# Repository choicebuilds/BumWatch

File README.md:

# BumWatch

THIS WATCH CONSISTS ENTIRELY OF BREAKOUT BOARDS AND IN-HOUSE FABRICATED PCBs. I was unable to make this version work on a PCB due to voltage regulator issues. So, I switched to the protoboard. If you plan on replicating this project, please do yourself a favor and add a functional buck converter. I created a significantly improved version here: https://github.com/choicebuilds/JWatch

## Introduction

The Bumwatch is truly made for bums - it has all the features a bum needs and nothing else. A very minimalistic display displays two things - steps taken and their heart rate that updates every second. 

We live in a world full of distractions and bum-inducing items. Technology is specifically designed to make our lives easier, which is synonymous with making us more of a bum. Instead of bleeding-edge features, what a bum needs is an accountability partner that gives them only what they truly need.

The BumWatch provides the satisfaction of progress through step counting that updates live to provide instant gratification and feedback. Also, knowing the average resting heart rate is 60-100, this would motivate the bums to lower their heartrate through exercise because they become aware they are a bum. Finally, when the bum idles for too long, there is a vibration feedback that reminds them they are a bum. If you want to stop being a bum, there is no better method than to create this watch.

This iteration of the BumWatch is made entirely in-house and costed $0 (not including time and labor). The BumWatch consists entirely of breakout boards (that I borrowed) placed and stacked neatly and soldered to a custom-PCB that was created using in-house PCB fabrication machines (I could not complete this part, so I used protoboards). Although I would never recommend this method (due to problems I will address as we go on), it was fun planning and watching everything come to fruition.

## PCB Fabrication
Essentially, you can use any electrical CAD software (I used KiCAD) to create a schematic and layout. Then, you export the Front Side Copper (gbr), Back Side Copper (gbr), Edge Cuts (gbr), and Drill Files (drl). Why only these four? Well, the available PCB fabrication machines in-house (LPKF Protomat and Protolaser) from my local makerspace makes it extremely limited for a few reasons:

1. You cannot create vias - this makes layout extremely difficult since you have to cram everything on one side. In other words, every trace has to be on the back side since through-hole soldering without vias makes it so that the front side is not electrically connected. This also makes the watch larger than necessary.
2. You cannot create solder mask or silkscreen - not exactly an issue for fabrication, but a giant headache for soldering & assembly (more on the PCB assembly section).

Is it still doable? Absolutely.
Does it look cooler? Absolutely (lie).
Will I ever do it again? Absolutely NOT.
The time and effort spent on laying it out and assembling it highly outweighs just ordering a PCB from say JLCPCB. I was unable to do this since I was not able to order them on time (due to US customs taking forever) and falling victim to sunk cost.

We'll get to why I had to make two iterations (yet still failed to make the final version) down the line.

## Materials

1x Arduino Pro Mini (MUST BE 3.3V Version)
- Small lipo batteries usually say they supply 3.7V. However, it will drop down from 4.2V when fully charged to 3.0V when fully discharged until it eventually gives out. So, either the breakouts must be rated within the 3.0V-4.2V range or we must use a voltage regulator/buck converter. Nevertheless, it has to be a 3.3V rated version unless you use a step-up converter that can supply 5V. Update: the voltage regulator on this one also had a 1V-1.1V dropout, so I ended up using an Arduino Nano.

1x SSD1306 (4-pin display)
- This was the only display I could find that fit my desired form factor that I could find in-person. There were many more options online, but I settled on this one since this version of the watch is not exactly the final version I want to use (i.e. I did not care).

1x Sparkfun ICM-20948 Breakout (IMU)
- The disadvantage of this one over the BNO055 (this was so old and inaccurate it was unusable) is that there is no integrated sensor fusion, meaning it displays the raw IMU data. However, this sensor is much newer and much more accurate than all the alternatives I have considered. In essence, it is better in every way as long as I can write an accurate step counter algorithm.

1x Sparkfun MAX30101 + MAX32664 Breakout (Pulse Oximeter and HR Monitor)
- The cool thing about this breakout is that it has a MAX32664 attached to it. The sole purpose of that chip is to take the raw data from the MAX30101 and use its internal algorithm to display the heart rate without me having to write any algorithms - very convenient.

1x Sparkfun BPM085 Breakout (Pressure Sensor)
- This ended up not being used in the final design because it was the only sensor rated at 1.8V-3.6V and the voltage regulator was a piece of junk. Also, I forgot to route the voltage regulator to the on/off switch meaning this sensor would always be on with the voltage regulator - as mentioned in the PCB Fabrication section, I ran out of time so I could not fix this issue.

1x Adafruit DRV2605L Breakout
- Every sensor above gave me a headache at some point for one reason or another, but this one just worked. Maybe Adafruit is superior to Sparkfun? (this is a joke.. or is it)

1x Vibration Motor
- Okay I lied, this isn't a breakout. But like you need a vibration motor to use the vibration motor driver right? This one is brand agnostic - just find a small vibration motor that fits your watch.

1x Adafruit USB-C Microlipo Breakout (USB-C Charging)
- Essentially, you can use this to charge/discharge your battery. It's only supports charging though, you do not use this to update your Arduino firmware. And also, it just works (to be fair, all the Sparkfun sensors had more complex wiring diagrams)

1x 3.3V Voltage Regulator
- I got this from my local makerspace and it was really, REALLY bad. The voltage drop after connecting one sensor was so large my multimeter displayed <3V (???). Luckily, all the sensors here except the BMP085 were rated 3V-5.5V, so I did not need this voltage regulator (i.e. I could connect it directly to the battery since it will always stay within 3V-4.2V.. update: the pro mini also had a terrible voltage regulator that outputted something along 2.7V). Due to this garbage of a regulator, I had to redo my entire layout and print an entire new circuit boards just because this voltage regulator was so bad (rant over). Why not use a buck converter? Simplicity and form factor of course. Also, this only crossed my mind after I created a layout that fit the smartwatch form factor. And considering this was not even the final version, I just could not bother to waste any more time on this. Please use a buck converter.

1x 3.7V LiPo Battery
- Pretty self-explanatory here, just find one that's not a coincell battery and is small enough to fit inside your watch.

1x On/Off Switch
- This can be any switch. It essentially creates an open circuit between the battery and all the sensors in order to save power when not used.

1x FTDL Basic Breakout (USB to Serial Converter)
- THIS IS NOT APART OF THE WATCH. The Arduino pro mini does not have a convenient port to update the firmware. So, you actually need this breakout to be able to push your Arduino sketches into the Arduino pro mini.

## Assembly

This part was a massive headache. I've soldered on a PCB with no solder mask or silkscreen before, but this one just caused a lot more problems than I would have liked. This was exponentially harder than the one I made before due to a lot of issues:

1. Not everything is connected in the layout - the first layout was perfect and everything would have worked out if the voltage regulator did not have problems. However, the second layout was made throughout an all-nighter the day before my local makerspace was going to close. I thought of a brilliant plan to bypass vias because things were not connecting properly on time. Instead of connecting everything on the back side, I decided to connect all my 3.7V on the front side and create a singular via with a very short wire and solder to connect the front and back side. This only works if there are vias for every 3.7V holes. Since the makerspace was closed, I could not make another PCB with a proper layout.

2. Misplaced sensors and improper traces - I flipped the pressure sensor backwards (it was right the first time, I don't even know how this happened) and the 3.7V on the voltage regulator comes straight from the battery instead of the on/off switch. I decided to add an on/off switch last minute, and I probably should not have made major changes before the deadline.

3.  The pins are pre-soldered onto the breakout - this should not have been a problem if problems 1 and 2 did not exist. However, in order to connect the 3.7V on the front side and remove a few pins to make layout easier (and more compact), I had to unsolder the pins and resolder them back together to connect them properly. Lesson learned - always, always double check your design before fabrication and do not trust your brain during an all-nighter.

4. The through-hole copper is fragile - since I was not sure I had access to flux after the makerspace closed, I sanded the final PCB very hard with sandpaper over running water to prevent oxidation. Bad idea. After soldering, the copper surrounding the all the through-holes would fall off with the sensors if I yanked too hard. Either that or it probably happened due to having to unsolder/resolder many things due to the issues mentioned above. So, I had to manually create traces whenever this happened.

5. Continuity Issues - I learned from the previous PCB I fabricated to make huge clearances. However, I finished half of it and came back after a week to realize there were my GND was connected to my SCL pin for some reason (?). After using an exacto knife to scratch around every single contact point, it was not a problem; but, the lack of solder mask and silkscreen is truly a pain.

You can stack the breakout boards together to reduce space. Also, you can cut the wires after soldering them to make them take up less space.

## Software

This part is extremely simple - it was a matter of copying preexisting libraries from the breakout boards and piecing them together. Here are the libraries for reference:

Display: https://github.com/adafruit/Adafruit_SSD1306
IMU: https://github.com/sparkfun/SparkFun_ICM-20948_ArduinoLibrary
HR Sensor: https://github.com/sparkfun/SparkFun_Bio_Sensor_Hub_Library
Pressure Sensor: https://github.com/adafruit/Adafruit-BMP085-Library
Vibration Motor: https://github.com/adafruit/Adafruit_DRV2605_Library

The only difficult part was processing the IMU data and creating a step counting algorithm. With the help of AI, I essentially combined the movement of all axes and if that was greater than a certain threshold, it was counted as a step. Then, I set a cooldown period based on the average human step pace in order to avoid double counting. This only works if the user is actively swinging their arms while walking - putting your hands in your pocket would lead to inaccurate results. Considering this is a first prototype, I was satisfied with this.

## Mechanical CAD (3D Printing)

If I did not have to redesign everything due to my voltage regulator, this would have looked much better. However, due to the frustration of everything stated above, I just created a bare minimum chassis for a working demo. Even then, it turns out I printed the wrong size before the 3D printing station had to shut down due to it being the end of the semester. Oh well.

## Protoboarding

With all the power issues, I still wanted to make a final product. So, I decided to create a 4-layer protoboard watch in order to fit a watch form factor. After hours of soldering, I got tired of continuity testing. This ultimately meant I could not use half the sensors because there were continuity issues for my lower 2 layers. However, I was still able to create a working IMU and step counter. This product is no longer in development & I will be focusing all my efforts on the JWatch (link above). Here are some pictures for reference:

## Conclusion

There are a lot of issues with this product. But all in all, with the fixes I mentioned above, I was able to create a functional product that works as intended, albeit not on the PCB. If anyone wants to expand upon this, please use a buck converter (step up if you wanna use 5V Arduinos, step down if you intend to use the pressure sensor or want consistent 3.3V output). Also, I would lay it out more compactly and properly with a professional PCB. Finally, the mechanical CAD is very bare-bones - there's much to improve in this aspect. I am satisfied with what I made since it was only a stepping stone to something bigger. I believe replicating this project as-is and making a working final product would be very helpful if you want to sharpen your debugging skills (please don't, you'll lose your hair over this).

## Working Demo

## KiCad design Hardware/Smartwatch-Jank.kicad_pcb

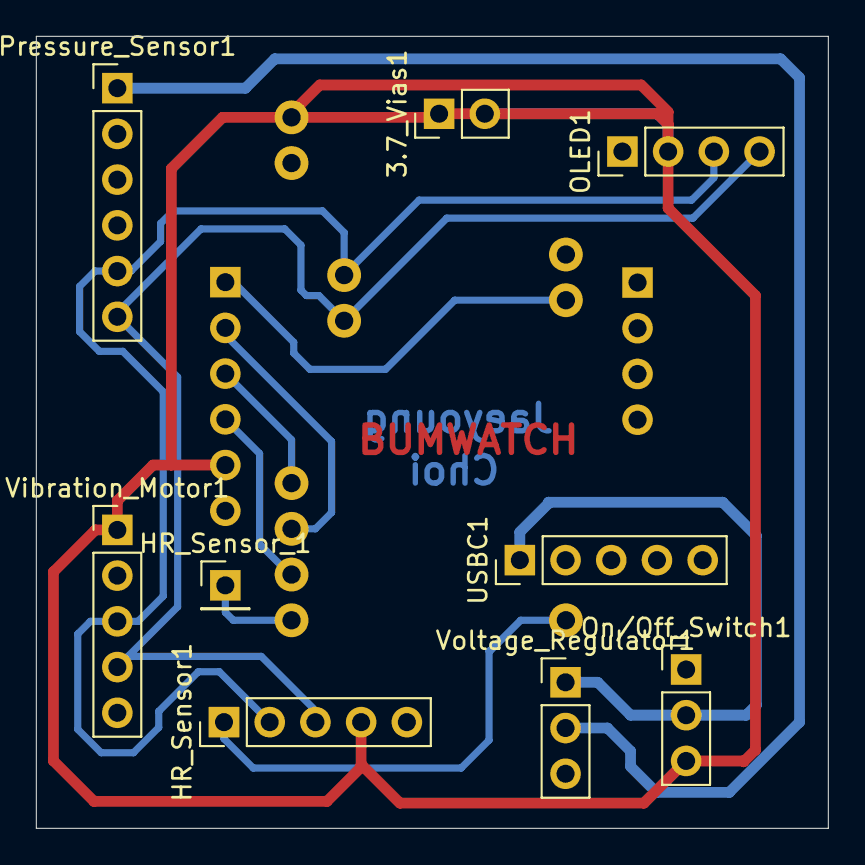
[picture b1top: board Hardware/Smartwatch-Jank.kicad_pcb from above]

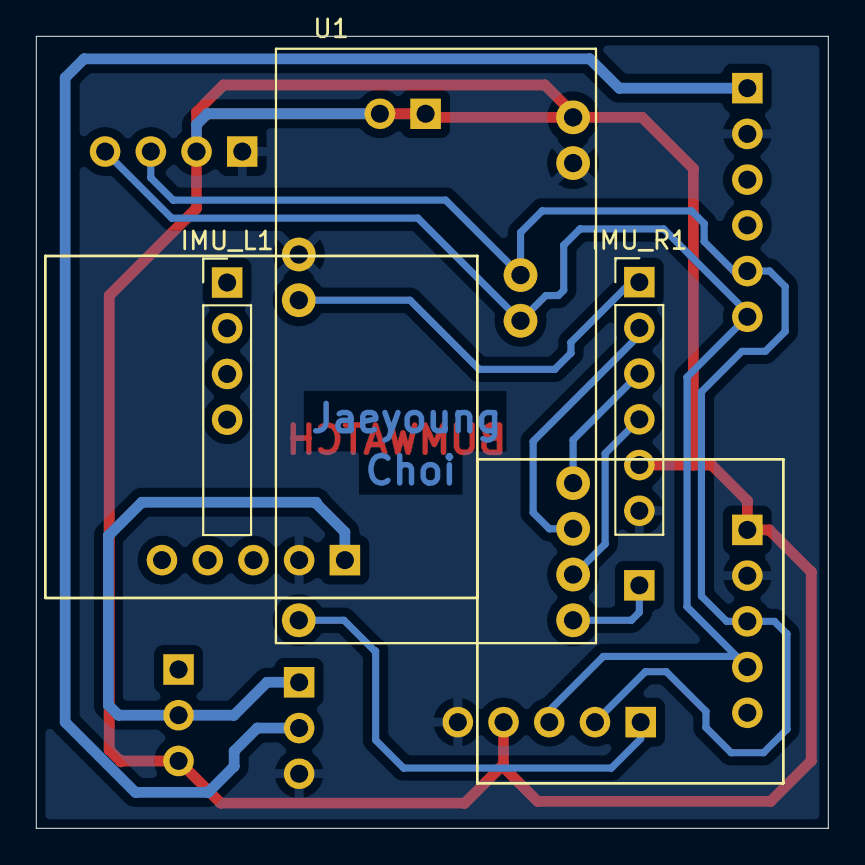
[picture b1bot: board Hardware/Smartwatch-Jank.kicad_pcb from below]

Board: 4 copper layers, 44.0 x 44.0 mm, 12 parts (3 on the bottom side), 12 nets.

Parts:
3.7_Vias1: Conn_01x02; PinHeader_1x02_P2.54mm_Vertical
HR_Sensor1: Conn_01x05; PinHeader_1x05_P2.54mm_Vertical
HR_Sensor_1: Conn_01x01; PinHeader_1x01_P2.54mm_Vertical
IMU_L1: Conn_01x06; PinHeader_1x06_P2.54mm_Vertical
IMU_R1: Conn_01x06; PinHeader_1x06_P2.54mm_Vertical
OLED1: Conn_01x04; PinHeader_1x04_P2.54mm_Vertical
On/Off_Switch1: Conn_01x03; PinHeader_1x03_P2.54mm_Vertical
Pressure_Sensor1: Conn_01x06; PinHeader_1x06_P2.54mm_Vertical
U1: ARDUINO_PRO_MINI; MODULE_ARDUINO_PRO_MINI
USBC1: Conn_01x05; PinHeader_1x05_P2.54mm_Vertical
Vibration_Motor1: Conn_01x05; PinHeader_1x05_P2.54mm_Vertical
Voltage_Regulator1: Conn_01x03; PinHeader_1x03_P2.54mm_Vertical

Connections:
/3.3: Pressure_Sensor1.1, Voltage_Regulator1.2
/3.7: 3.7_Vias1.1, 3.7_Vias1.2, HR_Sensor1.4, IMU_R1.5, OLED1.2, On/Off_Switch1.3, U1.JP6_1 (RAW), Vibration_Motor1.1
/BAT: On/Off_Switch1.2, USBC1.1, Voltage_Regulator1.1
/CS: IMU_R1.1, U1.JP7_8 (D2)
/D9: HR_Sensor1.1, U1.JP7_1 (D9)
/D10: HR_Sensor_1.1, U1.JP6_12 (D10)
/MISO: IMU_R1.2, U1.JP6_10 (MISO)
/MOSI: IMU_R1.4, U1.JP6_11 (MOSI)
/SCK: IMU_R1.3, U1.JP6_9 (SCK)
/SCL: HR_Sensor1.2, OLED1.3, Pressure_Sensor1.5, U1.JP2_2 (A5), Vibration_Motor1.3
/SDA: HR_Sensor1.3, OLED1.4, Pressure_Sensor1.6, U1.JP2_1 (A4), Vibration_Motor1.4
GND: HR_Sensor1.5, IMU_R1.6, OLED1.1, Pressure_Sensor1.2, U1.JP6_2 (GND_1), U1.JP7_9 (GND_2), USBC1.2, Vibration_Motor1.2, Voltage_Regulator1.3

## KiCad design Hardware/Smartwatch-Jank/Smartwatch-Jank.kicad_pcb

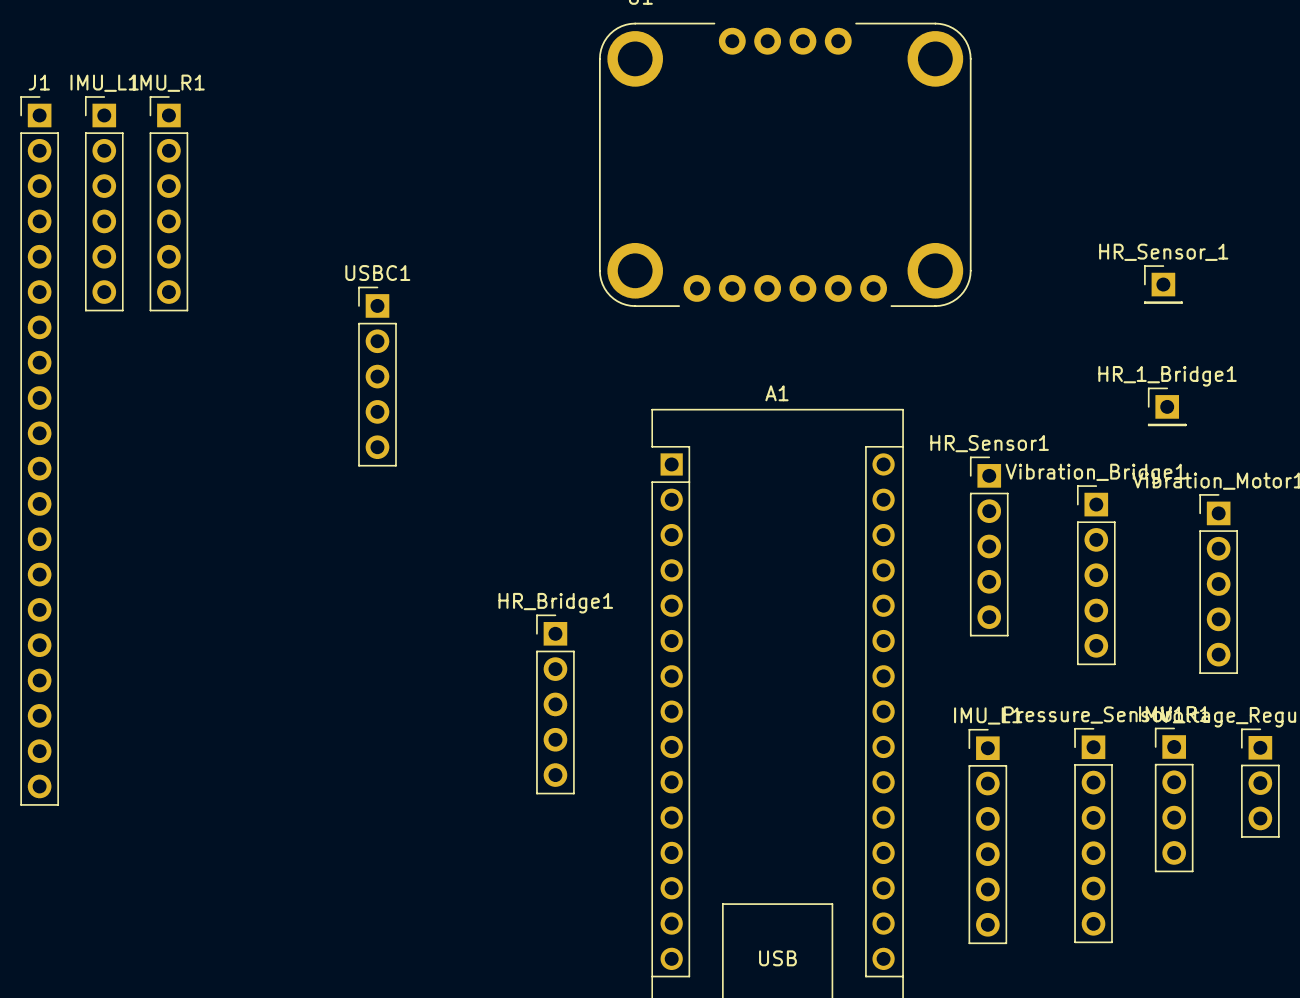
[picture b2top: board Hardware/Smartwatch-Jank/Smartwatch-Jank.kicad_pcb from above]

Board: 4 copper layers, 16 parts (0 on the bottom side), 21 nets, no tracks yet.

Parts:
A1: Arduino_Nano_Every; Arduino_Nano
HR_1_Bridge1: Conn_01x01; PinHeader_1x01_P2.54mm_Vertical
HR_Bridge1: Conn_01x05; PinHeader_1x05_P2.54mm_Vertical
HR_Sensor1: Conn_01x05; PinHeader_1x05_P2.54mm_Vertical
HR_Sensor_1: Conn_01x01; PinHeader_1x01_P2.54mm_Vertical
IMU_L1, IMU_L1#2: Conn_01x06; PinHeader_1x06_P2.54mm_Vertical
IMU_R1: Conn_01x06; PinHeader_1x06_P2.54mm_Vertical
IMU_R1#2: Conn_01x04; PinHeader_1x04_P2.54mm_Vertical
J1: Conn_01x20; PinHeader_1x20_P2.54mm_Vertical
Pressure_Sensor1: Conn_01x06; PinHeader_1x06_P2.54mm_Vertical
U1: 2472; BNO055
USBC1: Conn_01x05; PinHeader_1x05_P2.54mm_Vertical
Vibration_Bridge1: Conn_01x05; PinHeader_1x05_P2.54mm_Vertical
Vibration_Motor1: Conn_01x05; PinHeader_1x05_P2.54mm_Vertical
Voltage_Regulator1: Conn_01x03; PinHeader_1x03_P2.54mm_Vertical

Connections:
/3.3: HR_Sensor1.4, IMU_L1.5, J1.19, Pressure_Sensor1.1, U1.2 (3VO), Vibration_Motor1.1, Voltage_Regulator1.2
/3.7: USBC1.1, Voltage_Regulator1.1
/CCS: A1.10 (D7), J1.2
/CS: A1.5 (D2), IMU_L1.1, J1.14
/D8: A1.11 (D8), HR_Sensor1.1
/D9: A1.12 (D9), HR_Sensor_1.1
/D10: IMU_R1#2.3, U1.8 (INT)
/D/C: A1.6 (D3), J1.13
/GND: A1.4 (GND), A1.29 (GND), HR_Sensor1.5, IMU_L1.6, J1.20, Pressure_Sensor1.2, USBC1.2, Vibration_Motor1.2, Voltage_Regulator1.3
/Lite: A1.9 (D6), J1.11
/MISO: A1.15 (MISO), IMU_L1.2, J1.16
/MOSI: A1.14 (MOSI), IMU_L1.4, J1.15
/RST: A1.3 (~RESET), J1.12
/SCK: A1.16 (SCK), IMU_L1.3, J1.17
/SCL: A1.24 (SCL/A5), HR_Sensor1.2, IMU_L1#2.5, Pressure_Sensor1.5, U1.5 (SCL), Vibration_Motor1.3
/SDA: A1.23 (SDA/A4), HR_Sensor1.3, IMU_L1#2.4, Pressure_Sensor1.6, U1.4 (SDA), Vibration_Motor1.4
/X+: A1.7 (D4), J1.9
/X-: A1.22 (A3), J1.7
/Y+: A1.21 (A2), J1.10
/Y-: A1.8 (D5), J1.8
GND: IMU_L1#2.3, U1.3 (GND)

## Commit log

2025-11-11 Add working Arduino code for vibration motor
2025-11-13 Add working arduino code for IMU
2025-11-13 Add working Arduino code for the MAX30101+MAX32664 breakout
2025-11-13 Add working Arduino code for pressure sensor
2025-11-16 Different IMU and code for better form factor
2025-11-16 Add full schematic with no ERC errors
2025-11-17 Replaced BNO055 to ICM20248 for more accurate IMU tracking
2025-11-18 Replace basic IMU code with step counting algorithm
2025-11-19 Add final PCB design for fabrication
2025-11-21 Add code for display
2025-11-21 Integrate step tracking with the display and add vibration
2025-11-24 Add new schematic with battery powering most sensors without voltage regulator
2025-12-08 Update README.md intro
2025-12-08 Update README.md materials
2025-12-08 Complete first draft of README.md
2025-12-09 Update README.md to reflect actual progress
2025-12-10 Update README.md to reflect final product
2025-12-10 Update README.md libraries list
2025-12-16 Update README.md protoboarding
2025-12-17 Add pictures
2025-12-17 Update README.md picture test
2025-12-17 Finish documentation with pictures
2025-12-18 Add working demo to README.md
2025-12-18 Fix faulty link in README.md
2025-12-23 Finalize README.md
